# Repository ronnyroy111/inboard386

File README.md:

# Intel Inboard 386/PC Clone
https://forum.theretroweb.com/t/intel-inboard-386-pc-accelerator-clone/44

This is a project to reverse engineer and reproduce the [Intel Inboard 386/PC Accelerator Card](https://theretroweb.com/expansioncards/s/intel-inboard-386-pc).  
It's based on a damaged card that i obtained a while ago and managed to fix but decided to sacrifice for a reproduction.  
The Inboard 386/PC is an upgrade card from Intel for the IBM PC/XT and clones that upgraded the 8088 CPU to a 16MHz 386DX and up to 5MB of system memory.  
The card only uses standard 74 series logic chips along with some PALs/PROMs that were luckily not secured and were successfully dumped.  
The PCB is a 6 layer design with 4 signal layers. To aid with reverse engineering it i ended up choosing the destructive route and sanded the entire PCB down to the inner layers.  
By now the PCB design has been completed while the schematic still needs cleanup and further reverse engineering of the programmable logic to completely understand.  

The first revision of the board has been tested and confirmed to be working.  
GAL replacements for the PAL chips and a PROM replacement board have been tested as well.  
  
A memory expansion board is currently in work.

This current board design is a 1:1 copy of the original PCB, excluding some small details.  
A future plan is to do a redesign to condense parts of the logic into one or more CPLDs and integrate the optional external memory expansion boards into the design

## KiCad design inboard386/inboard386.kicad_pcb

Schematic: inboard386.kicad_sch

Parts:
C1, C2, C3, C4, C5, C6, C7, C8, C9, C10, C11, C12, C13, C14, C15, C16, C17, C18, C19, C20, C21, C22, C23, C24, C25, C26, C27, C28, C29, C30, C31, C32, C33, C34, C35, C36, C37, C38, C39, C40, C41, C42, C43, C44, C45, C46, C47, C48, C49, C50, C51, C53, C54, C55, C56, C57, C58, C59, C62, C63, C64, C66, C67, C68, C69, C70, C71, C72, C73: 100nF; C_Axial_L3.8mm_D2.6mm_P7.62mm_Horizontal_layer
C52: 22pF; C_Axial_L3.8mm_D2.6mm_P7.62mm_Horizontal_layer
C60, C61: 180pF; C_Axial_L3.8mm_D2.6mm_P7.62mm_Horizontal_layer
C65: 560µF; CP_Axial_L21.0mm_D8.0mm_P28.00mm_Horizontal_layer
CR1: 390 mV; D_DO-35_SOD27_P10.16mm_Horizontal_layer
H1, H2: MountingHole_Pad; MountingHole_3.2mm_M3_DIN965_Pad
J1, J2: Conn_02x20_Odd_Even; PinHeader_2x20_P2.54mm_inboard_mem
J3: CPU_Cable; IDC-Header_2x20_P2.54mm_Vertical_layer
J4: Bus_ISA_8bit; BUS_PC
R1: 115; R_Axial_DIN0207_L6.3mm_D2.5mm_P10.16mm_Horizontal_layer
R2: 12; R_Axial_DIN0207_L6.3mm_D2.5mm_P10.16mm_Horizontal_layer
R3: 1k; R_Axial_DIN0207_L6.3mm_D2.5mm_P10.16mm_Horizontal_layer
RP1, RP2, RP9, RP10: 2.2k; R_Array_SIP10_layer
RP3, RP4, RP5, RP6, RP7, RP8: 22; R_Array_SIP8_layer
RP11: 100; R_Array_SIP10_layer
RP12: 10k; R_Array_SIP10_layer
RP13, RP14: 3.3k; R_Array_SIP10_layer
U1, U2, U3, U4, U5, U6, U7, U8, U9, U10, U11, U12, U13, U14, U15, U16, U17, U18, U19, U20, U21, U22, U23, U24, U25, U26, U27, U28, U29, U30, U31, U32, U33, U34, U35, U36: TMM41256AP; DIP-16_W7.62mm_layer
U37, U38, U40, U44: 74F280; DIP-14_W7.62mm_layer
U39, U41, U78: 74AS1004; DIP-14_W7.62mm_layer
U42, U43: 74AS1032; DIP-14_W7.62mm_layer
U45, U62, U63, U66, U67, U92, U93: 74F74; DIP-14_W7.62mm_layer
U46, U48, U50, U53, U90: 74ALS244; DIP-20_W7.62mm_layer
U47, U49, U51, U52, U96, U97: 74ALS373; DIP-20_W7.62mm_layer
U54: 74F244; DIP-20_W7.62mm_layer
U55, U56, U57, U72, U95: 74ALS245; DIP-20_W7.62mm_layer
U58: 74F32; DIP-14_W7.62mm_layer
U59: 74AS21; DIP-14_W7.62mm_layer
U60: 74F00; DIP-14_W7.62mm_layer
U61, U64, U81, U82: 74F258; DIP-16_W7.62mm_layer
U65: 74AS1000; DIP-14_W7.62mm_layer
U68: 74F153; DIP-16_W7.62mm_layer
U69: 74LS174; DIP-16_W7.62mm_layer
U70: PAL16R8; DIP-20_W7.62mm_layer
U71: PAL20L8; DIP-24_W7.62mm_layer
U73: 80386; PGA-132_14x14_37.0x37.0mm
U74: PAL16R4; DIP-20_W7.62mm_layer
U75, U76: PAL16R6; DIP-20_W7.62mm_layer
U77, U84, U87, U91, U100: PAL16L8; DIP-20_W7.62mm_layer
U79: 74LS30; DIP-14_W7.62mm_layer
U80: 74F161; DIP-16_W7.62mm_layer
U83: 32MHz; Oscillator_DIP-14_layer
U85: 80387; PGA-68_11x11_29.2x29.2mm
U86, U101: TIBPAL16R4; DIP-20_W7.62mm_layer
U88, U89: 74ALS374; DIP-20_W7.62mm_layer
U94: 74F08; DIP-14_W7.62mm_layer
U98: 63S281; DIP-20_W7.62mm_layer
U99: TIBPAL16L8; DIP-20_W7.62mm_layer
U102: TIBPAL16R6; DIP-20_W7.62mm_layer

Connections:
387_ERR: U63.8 (~Q), U94.4
8088D_Cp: U86.1 (CLK), U89.11 (Cp), U100.16 (I/~O_{5})
8088D_OE: U89.1 (OE), U100.15 (I/~O_{4})
8088_A8: J3.16 (A8), U96.2 (O0)
8088_A9: J3.14 (A9), U96.5 (O1)
8088_A10: J3.12 (A10), U96.6 (O2)
8088_A11: J3.10 (A11), U96.9 (O3)
8088_A12: J3.8 (A12), U96.12 (O4)
8088_A13: J3.6 (A13), U96.15 (O5)
8088_A14: J3.4 (A14), U96.16 (O6)
8088_A15: J3.3 (A15), U96.19 (O7)
8088_A16/S3: J3.5 (A16/S3), U97.2 (O0)
8088_A17/S4: J3.7 (A17/S4), U97.5 (O1)
8088_A18/S5: J3.9 (A18/S5), U97.6 (O2)
8088_A19/S6: J3.11 (A19/S6), U97.9 (O3)
8088_AD0: J3.32 (AD0), U88.3 (D0), U89.2 (O0), U90.3 (O3b)
8088_AD1: J3.30 (AD1), U89.5 (O1), U90.5 (O2b), U94.1
8088_AD2: J3.28 (AD2), U88.7 (D2), U89.6 (O2), U90.18 (O0a)
8088_AD3: J3.26 (AD3), U88.8 (D3), U89.9 (O3), U90.16 (O1a)
8088_AD4: J3.24 (AD4), U88.13 (D4), U89.12 (O4), U90.14 (O2a)
8088_AD5: J3.22 (AD5), U88.14 (D5), U89.15 (O5), U90.12 (O3a)
8088_AD6: J3.20 (AD6), U88.17 (D6), U89.16 (O6), U90.9 (O0b)
8088_AD7: J3.18 (AD7), U88.18 (D7), U89.19 (O7), U90.7 (O1b)
8088_ALE: U70.17 (~O_{6}), U96.11 (LE), U97.11 (LE), U100.5 (I_{4})
+5V: C1.1, C2.1, C3.1, C4.1, C5.1, C6.1, C7.1, C8.1, C9.1, C10.1, C11.1, C12.1, C13.1, C14.1, C15.1, C16.1, C17.1, C18.1, C19.1, C20.1, C21.1, C22.1, C23.1, C24.1, C25.1, C26.1, C27.1, C28.1, C29.1, C30.1, C31.1, C32.1, C33.1, C34.1, C35.1, C36.1, C37.1, C38.1, C39.1, C40.1, C41.1, C42.1, C43.1, C44.1, C45.1, C46.1, C47.1, C48.1, C49.1, C50.1, C51.1, C53.1, C54.1, C55.1, C56.1, C57.1, C58.1, C59.1, C62.1, C63.1, C64.1, C65.1, C66.1, C67.1, C68.1, C69.1, C70.1, C71.1, C72.1, C73.1, CR1.1 (K), J1.5, J1.17, J1.29, J1.39, J2.9, J2.13, J2.17, J2.21, J2.29, J3.1 (VCC), J4.3 (VCC), J4.29 (VCC), R1.1, RP1.1 (common), RP2.1 (common), RP9.1 (common), RP10.1 (common), RP12.1 (common), RP13.1 (common), RP14.1 (common), U1.8 (V_{CC}), U2.8 (V_{CC}), U3.8 (V_{CC}), U4.8 (V_{CC}), U5.8 (V_{CC}), U6.8 (V_{CC}), U7.8 (V_{CC}), U8.8 (V_{CC}), U9.8 (V_{CC}), U10.8 (V_{CC}), U11.8 (V_{CC}), U12.8 (V_{CC}), U13.8 (V_{CC}), U14.8 (V_{CC}), U15.8 (V_{CC}), U16.8 (V_{CC}), U17.8 (V_{CC}), U18.8 (V_{CC}), U19.8 (V_{CC}), U20.8 (V_{CC}), U21.8 (V_{CC}), U22.8 (V_{CC}), U23.8 (V_{CC}), U24.8 (V_{CC}), U25.8 (V_{CC}), U26.8 (V_{CC}), U27.8 (V_{CC}), U28.8 (V_{CC}), U29.8 (V_{CC}), U30.8 (V_{CC}), U31.8 (V_{CC}), U32.8 (V_{CC}), U33.8 (V_{CC}), U34.8 (V_{CC}), U35.8 (V_{CC}), U36.8 (V_{CC}), U37.14 (VCC), U38.14 (VCC), U39.14 (VCC), U40.14 (VCC), U41.14 (VCC), U42.14 (VCC), U43.14 (VCC), U44.14 (VCC), U45.14 (VCC), U46.20 (VCC), U47.20 (VCC), U48.20 (VCC), U49.20 (VCC), U50.20 (VCC), U51.20 (VCC), U52.20 (VCC), U53.20 (VCC), U54.4 (I1a), U54.20 (VCC), U55.20 (VCC), U56.20 (VCC), U57.20 (VCC), U58.14 (VCC), U59.14 (VCC), U60.14 (VCC), U61.16 (VCC), U62.4 (~S), U62.13 (~R), U62.14 (VCC), U63.1 (~R), U63.13 (~R), U63.14 (VCC), U64.16 (VCC), U65.14 (VCC), U66.1 (~R), U66.4 (~S), U66.13 (~R), U66.14 (VCC), U67.10 (~S), U67.13 (~R), U67.14 (VCC), U68.16 (VCC), U69.14 (D5), U69.16 (VCC), U70.20 (V_{CC}), U71.24 (V_{CC}), U72.20 (VCC), U73.A1 (VCC), U73.A5 (VCC), U73.A7 (VCC), U73.A10 (VCC), U73.A14 (VCC), U73.C5 (VCC), U73.C12 (VCC), U73.D12 (VCC), U73.G2 (VCC), U73.G3 (VCC), U73.G12 (VCC), U73.G14 (VCC), U73.L12 (VCC), U73.M3 (VCC), U73.M7 (VCC), U73.M13 (VCC), U73.N4 (VCC), U73.N7 (VCC), U73.P2 (VCC), U73.P8 (VCC), U74.20 (V_{CC}), U75.20 (V_{CC}), U76.20 (V_{CC}), U77.20 (V_{CC}), U78.14 (VCC), U79.14 (VCC), U80.10 (CET), U80.16 (VCC), U81.16 (VCC), U82.16 (VCC), U83.14 (Vcc), U84.20 (V_{CC}), U85.A6 (VCC), U85.A9 (VCC), U85.B4 (VCC), U85.E1 (VCC), U85.F1 (VCC), U85.F10 (VCC), U85.J2 (VCC), U85.J11 (CKM), U85.K3 (TIE_HIGH), U85.K5 (VCC), U85.L4 (STEN), U85.L7 (VCC), U85.L9 (TIE_HIGH), U86.20 (V_{CC}), U87.20 (V_{CC}), U88.20 (VCC), U89.20 (VCC), U90.20 (VCC), U91.20 (V_{CC}), U92.4 (~S), U92.10 (~S), U92.13 (~R), U92.14 (VCC), U93.1 (~R), U93.10 (~S), U93.13 (~R), U93.14 (VCC), U94.14 (VCC), U95.20 (VCC), U96.20 (VCC), U97.20 (VCC), U98.20 (VCC), U99.20 (V_{CC}), U100.20 (V_{CC})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
A0: U70.15 (~O_{4}), U77.6 (I_{5}), U86.7 (I_{6}), U90.17 (I3b), U98.1 (A0), U99.2 (I_{1}), U100.7 (I_{6})
A1: U70.16 (~O_{5}), U77.5 (I_{4}), U86.6 (I_{5}), U90.15 (I2b), U98.2 (A1), U99.1 (I_{0}), U100.6 (I_{5})
A2: U64.13 (I1c), U73.C4 (A2), U74.5 (I_{4}), U85.L8 (CMD0#), U90.2 (I0a), U98.3 (A2), U100.8 (I_{7})
A3: U64.10 (I1d), U73.A3, U90.4 (I1a), U98.4 (A3)
A4: U64.6 (I1b), U73.B3 (A4), U90.6 (I2a), U98.5 (A4)
A5: U64.3 (I1a), U73.B2 (A5), U84.11 (I_{9}), U86.3 (I_{2}), U90.8 (I3a), U98.17 (A5)
A6: U61.13 (I1c), U73.C3 (A6), U84.9 (I_{8}), U90.11 (I0b), U98.18 (A6), U100.9 (I_{8}), U101.2 (I_{1})
A7: U61.10 (I1d), U73.C2 (A7), U84.8 (I_{7}), U90.13 (I1b), U98.19 (A7)
A8: U61.6 (I1b), U73.C1 (A8), U84.7 (I_{6}), U96.3 (D0)
A9: U64.14 (I0c), U73.D3 (A9), U84.6 (I_{5}), U96.4 (D1), U101.3 (I_{2})
A10: U64.11 (I0d), U73.D2 (A10), U84.5 (I_{4}), U96.7 (D2)
A11: U64.5 (I0b), U73.D1 (A11), U96.8 (D3)
A12: U64.2 (I0a), U73.E3 (A12), U96.13 (D4)
A13: U61.14 (I0c), U73.E2 (A13), U96.14 (D5)
A14: U61.11 (I0d), U73.E1 (A14), U96.17 (D6)
A15: U68.13 (I3b), U73.F1 (A15), U96.18 (D7)
A16: U68.3 (I3a), U71.7 (I_{6}), U73.G1 (A16), U97.3 (D0)
A17: U68.12 (I2b), U71.6 (I_{5}), U73.H1 (A17), U97.4 (D1)
A18: U71.5 (I_{4}), U73.H2 (A18), U97.7 (D2)
A19: U71.4 (I_{3}), U73.H3 (A19), U97.8 (D3)
A20: U61.2 (I0a), U71.3 (I_{2}), U73.J1 (A20)
A21: U61.3 (I1a), U71.2 (I_{1}), U73.K1 (A21)
A22: U71.1 (I_{0}), U73.K2 (A22)
A23: U71.8 (I_{7}), U73.L1 (A23)
A30: U73.P1 (A30), U97.17 (D6)
A30L: U58.5, U78.11, U97.16 (O6)
A31: U73.N2 (A31), U84.4 (I_{3}), U85.K6 (NPS2)
A->AD: U90.1 (OEa), U90.19 (OEb), U100.12 (~O_{1})
AEN: J4.42 (AEN), U58.1, U62.2 (D), U87.9 (I_{8}), U102.2 (I_{1})
AEN_BUF: U62.5 (Q), U75.5 (I_{4})
BA00: J4.62 (BA00), U91.8 (I_{7}), U99.4 (I_{3})
BA01: J4.61 (BA01), U91.9 (I_{8}), U99.3 (I_{2})
BA02: J4.60 (BA02), U82.13 (I1c)
BA03: J4.59 (BA03), U82.10 (I1d)
BA04: J4.58 (BA04), U82.6 (I1b)
BA05: J4.57 (BA05), U82.3 (I1a)
BA06: J4.56 (BA06), U81.13 (I1c)
BA07: J4.55 (BA07), U81.10 (I1d)
BA08: J4.54 (BA08), U81.6 (I1b)
BA09: J4.53 (BA09), U82.14 (I0c)
BA10: J4.52 (BA10), U82.11 (I0d)
BA11: J4.51 (BA11), U82.5 (I0b)
BA12: J4.50 (BA12), U82.2 (I0a)
BA13: J4.49 (BA13), U81.14 (I0c)
BA14: J4.48 (BA14), U81.11 (I0d)
BA15: J4.47 (BA15), U91.13 (I/~O_{2})
BA16: J4.46 (BA16), U91.18 (I/~O_{7})
BA17: J4.45 (BA17), U68.10 (I0b), U87.3 (I_{2})
BA18: J4.44 (BA18), U87.2 (I_{1})
BA19: J4.43 (BA19), U81.5 (I0b), U87.1 (I_{0})
BUSDIR: U55.1 (A->B), U56.1 (A->B), U57.1 (A->B), U72.1 (A->B), U95.1 (A->B), U99.15 (I/~O_{4})
CLK: U45.3 (C), U62.3 (C), U62.11 (C), U63.3 (C), U66.11 (C), U67.5 (Q), U74.6 (I_{5}), U75.9 (I_{8}), U76.9 (I_{8}), U80.2 (CP)
CLK2: R2.2, U66.3 (C), U67.3 (C), U67.11 (C), U73.F12 (CLK2), U74.1 (CLK), U75.1 (CLK), U76.1 (CLK), U85.K10 (CPUCLK2)
CLK88: C52.1, CR1.2 (A), J3.38 (CLK), R3.1, U78.1
CLK88_BUF: U78.4, U92.3 (C), U93.3 (C), U93.11 (C)
D0: U52.2 (O0), U53.17 (I3b), U69.3 (D0), U73.H12 (D0), U85.H2 (D0)
D1: U52.5 (O1), U53.15 (I2b), U69.4 (D1), U73.H13 (D1), U85.H1 (D1)
D2: U52.6 (O2), U53.13 (I1b), U69.6 (D2), U73.H14 (D2), U85.G2 (D2)
D3: U52.9 (O3), U53.11 (I0b), U69.11 (D3), U73.J14 (D3), U85.G1 (D3)
D4: U52.12 (O4), U53.8 (I3a), U69.13 (D4), U73.K14 (D4), U85.D2 (D4)
D5: U52.15 (O5), U53.6 (I2a), U73.K13 (D5), U85.D1 (D5)
D6: U52.16 (O6), U53.4 (I1a), U73.L14 (D6), U85.C2 (D6)
D7: U52.19 (O7), U53.2 (I0a), U73.K12 (D7), U85.C1 (D7)
D8: U50.17 (I3b), U51.2 (O0), U73.L13 (D8), U85.B1 (D8)
D9: U50.15 (I2b), U51.5 (O1), U73.N14 (D9), U85.A2 (D9)
D10: U50.13 (I1b), U51.6 (O2), U73.M12 (D10), U85.B3 (D10)
D11: U50.11 (I0b), U51.9 (O3), U73.N13 (D11), U85.A3 (D11)
D12: U50.8 (I3a), U51.12 (O4), U73.N12 (D12), U85.A4 (D12)
D13: U50.6 (I2a), U51.15 (O5), U73.P13 (D13), U85.B5 (D13)
D14: U50.4 (I1a), U51.16 (O6), U73.P12 (D14), U85.A5 (D14)
D15: U50.2 (I0a), U51.19 (O7), U73.M11 (D15), U85.B6 (D15)
D16: U48.17 (I3b), U49.2 (O0), U73.N11 (D16), U85.A7 (D16)
D17: U48.15 (I2b), U49.5 (O1), U73.N10 (D17), U85.B8 (D17)
D18: U48.13 (I1b), U49.6 (O2), U73.P11 (D18), U85.A8 (D18)
D19: U48.11 (I0b), U49.9 (O3), U73.P10 (D19), U85.B9 (D19)
D20: U48.8 (I3a), U49.12 (O4), U73.M9 (D20), U85.B10 (D20)
D21: U48.6 (I2a), U49.15 (O5), U73.N9 (D21), U85.A10 (D21)
D22: U48.4 (I1a), U49.16 (O6), U73.P9 (D22), U85.B11 (D22)
D23: U48.2 (I0a), U49.19 (O7), U73.N8 (D23), U85.C10 (D23)
D24: U46.17 (I3b), U47.2 (O0), U73.P7 (D24), U85.D10 (D24)
D25: U46.15 (I2b), U47.5 (O1), U73.N6 (D25), U85.D11 (D25)
D26: U46.13 (I1b), U47.6 (O2), U73.P5 (D26), U85.E10 (D26)
D27: U46.11 (I0b), U47.9 (O3), U73.N5 (D27), U85.E11 (D27)
D28: U46.8 (I3a), U47.12 (O4), U73.M6 (D28), U85.G10 (D28)
D29: U46.6 (I2a), U47.15 (O5), U73.P4 (D29), U85.G11 (D29)
D30: U46.4 (I1a), U47.16 (O6), U73.P3 (D30), U85.H10 (D30)
D31: U46.2 (I0a), U47.19 (O7), U73.M5 (D31), U85.H11 (D31)
D->MD_OE: U46.1 (OEa), U46.19 (OEb), U48.1 (OEa), U48.19 (OEb), U50.1 (OEa), U50.19 (OEb), U53.1 (OEa), U53.19 (OEb), U60.8
DACK0: U71.11 (I_{10}), U74.18 (I/~O_{7}), U78.8, U87.11 (I_{9}), U91.6 (I_{5})
DB0: J4.40 (DB0), RP13.3 (R2), U95.18 (B0)
DB0B: RP14.9 (R8), U55.18 (B0), U56.18 (B0), U57.18 (B0), U72.18 (B0), U79.1, U88.2 (O0), U89.3 (D0), U95.2 (A0), U98.6 (O1)
DB1: J4.39 (DB1), RP13.4 (R3), U95.17 (B1)
DB1B: RP14.8 (R7), U55.17 (B1), U56.17 (B1), U57.17 (B1), U72.17 (B1), U88.5 (O1), U89.4 (D1), U95.3 (A1), U98.7 (O2), U102.8 (I_{7})
DB2: J4.38 (DB2), RP13.5 (R4), U95.16 (B2)
DB2B: RP14.7 (R6), U55.16 (B2), U56.16 (B2), U57.16 (B2), U72.16 (B2), U79.2, U86.2 (I_{1}), U88.6 (O2), U95.4 (A2), U98.8 (O3)
DB3: J4.37 (DB3), RP13.6 (R5), U95.15 (B3)
DB3B: RP14.6 (R5), U55.15 (B3), U56.15 (B3), U57.15 (B3), U72.15 (B3), U79.3, U86.19 (I/~O_{8}), U88.9 (O3), U89.8 (D3), U95.5 (A3), U98.9 (O4)
DB4: J4.36 (DB4), RP13.7 (R6), U95.14 (B4)
DB4B: RP14.5 (R4), U55.14 (B4), U56.14 (B4), U57.14 (B4), U72.14 (B4), U79.4, U88.12 (O4), U89.13 (D4), U95.6 (A4), U98.11 (O5)
DB5: J4.35 (DB5), RP13.8 (R7), U95.13 (B5)
DB5B: RP14.4 (R3), U55.13 (B5), U56.13 (B5), U57.13 (B5), U72.13 (B5), U88.15 (O5), U89.14 (D5), U95.7 (A5), U98.12 (O6), U102.7 (I_{6})
DB6: J4.34 (DB6), RP13.9 (R8), U95.12 (B6)
DB6B: RP14.3 (R2), U55.12 (B6), U56.12 (B6), U57.12 (B6), U72.12 (B6), U79.5, U88.16 (O6), U89.17 (D6), U95.8 (A6), U98.13 (O7)
DB7: J4.33 (DB7), RP13.10 (R9), U95.11 (B7)
DB7B: RP14.2 (R1), U55.11 (B7), U56.11 (B7), U57.11 (B7), U72.11 (B7), U79.6, U86.18 (I/~O_{7}), U88.19 (O7), U89.18 (D7), U95.9 (A7), U98.14 (O8)
DB_EN: U87.12 (~O_{1}), U95.19 (CE)
D/~C: U73.A11 (D/~C), U77.9 (I_{8}), U84.2 (I_{1})
ERROR387: U63.11 (C), U78.6
FPU_STAT_SET: U42.13, U63.10 (~S), U74.16 (~O_{5})
GND: C1.2, C2.2, C3.2, C4.2, C5.2, C6.2, C7.2, C8.2, C9.2, C10.2, C11.2, C12.2, C13.2, C14.2, C15.2, C16.2, C17.2, C18.2, C19.2, C20.2, C21.2, C22.2, C23.2, C24.2, C25.2, C26.2, C27.2, C28.2, C29.2, C30.2, C31.2, C32.2, C33.2, C34.2, C35.2, C36.2, C37.2, C38.2, C39.2, C40.2, C41.2, C42.2, C43.2, C44.2, C45.2, C46.2, C47.2, C48.2, C49.2, C50.2, C51.2, C53.2, C54.2, C55.2, C56.2, C57.2, C58.2, C59.2, C60.2, C61.2, C62.2, C63.2, C64.2, C65.2, C66.2, C67.2, C68.2, C69.2, C70.2, C71.2, C72.2, C73.2, H1.1 (1_1), H2.1 (1_1), J1.2, J1.12, J1.24, J1.36, J2.2, J2.12, J2.16, J2.20, J2.28, J2.40, J3.2 (GND), J3.40 (GND), J4.1 (GND), J4.10 (GND), J4.31 (GND), R3.2, RP6.5 (R3.1), RP11.1 (common), U1.16 (V_{SS}), U2.16 (V_{SS}), U3.16 (V_{SS}), U4.16 (V_{SS}), U5.16 (V_{SS}), U6.16 (V_{SS}), U7.16 (V_{SS}), U8.16 (V_{SS}), U9.16 (V_{SS}), U10.16 (V_{SS}), U11.16 (V_{SS}), U12.16 (V_{SS}), U13.16 (V_{SS}), U14.16 (V_{SS}), U15.16 (V_{SS}), U16.16 (V_{SS}), U17.16 (V_{SS}), U18.16 (V_{SS}), U19.16 (V_{SS}), U20.16 (V_{SS}), U21.16 (V_{SS}), U22.16 (V_{SS}), U23.16 (V_{SS}), U24.16 (V_{SS}), U25.16 (V_{SS}), U26.16 (V_{SS}), U27.16 (V_{SS}), U28.16 (V_{SS}), U29.16 (V_{SS}), U30.16 (V_{SS}), U31.16 (V_{SS}), U32.16 (V_{SS}), U33.16 (V_{SS}), U34.16 (V_{SS}), U35.16 (V_{SS}), U36.16 (V_{SS}), U37.7 (GND), U38.7 (GND), U39.7 (GND), U40.7 (GND), U41.7 (GND), U42.7 (GND), U43.7 (GND), U44.7 (GND), U45.7 (GND), U46.10 (GND), U47.10 (GND), U48.10 (GND), U49.10 (GND), U50.10 (GND), U51.10 (GND), U52.10 (GND), U53.10 (GND), U54.2 (I0a), U54.6 (I2a), U54.8 (I3a), U54.10 (GND), U54.11 (I0b), U54.13 (I1b), U54.15 (I2b), U54.17 (I3b), U55.10 (GND), U56.10 (GND), U57.10 (GND), U58.7 (GND), U59.7 (GND), U60.7 (GND), U61.8 (GND), U62.7 (GND), U63.7 (GND), U63.12 (D), U64.8 (GND), U65.7 (GND), U66.7 (GND), U67.7 (GND), U68.8 (GND), U69.8 (GND), U70.10 (GND), U71.12 (GND), U72.10 (GND), U73.A2 (VSS), U73.A6 (VSS), U73.A9 (VSS), U73.B1 (VSS), U73.B5 (VSS), U73.B11 (VSS), U73.B14 (VSS), U73.C11 (VSS), U73.F2 (VSS), U73.F3 (VSS), U73.F14 (VSS), U73.J2 (VSS), U73.J3 (VSS), U73.J12 (VSS), U73.J13 (VSS), U73.M4 (VSS), U73.M8 (VSS), U73.M10 (VSS), U73.N3 (VSS), U73.P6 (VSS), U73.P14 (VSS), U74.10 (GND), U75.10 (GND), U76.10 (GND), U77.10 (GND), U78.7 (GND), U79.7 (GND), U80.8 (GND), U81.2 (I0a), U81.3 (I1a), U81.8 (GND), U82.8 (GND), U83.7 (GND), U84.10 (GND), U85.B2 (VSS), U85.B7 (VSS), U85.C11 (VSS), U85.E2 (VSS), U85.F2 (VSS), U85.F11 (VSS), U85.J1 (VSS), U85.J10 (VSS), U85.K9 (NC), U85.K11 (NUMCLK2), U85.L5 (VSS), U86.10 (GND), U87.10 (GND), U88.10 (GND), U89.10 (GND), U90.10 (GND), U91.10 (GND), U92.7 (GND), U93.7 (GND), U94.7 (GND), U95.10 (GND), U96.10 (GND), U97.10 (GND), U98.10 (GND), U99.10 (GND), U100.10 (GND), U101.10 (GND), U102.10 (GND)
HOLD: RP11.4 (R3), U73.D14 (HOLD)
INTR: U73.B7 (INTR), U101.19 (I/~O_{8})
INTR88: C61.1, J3.36 (INTR), U101.9 (I_{8})
IO: J4.32 (IO), U87.16 (I/~O_{5})
MA0: RP4.4 (R2.2), U1.5 (A0), U2.5 (A0), U3.5 (A0), U4.5 (A0), U5.5 (A0), U6.5 (A0), U7.5 (A0), U8.5 (A0), U9.5 (A0), U10.5 (A0), U11.5 (A0), U12.5 (A0), U13.5 (A0), U14.5 (A0), U15.5 (A0), U16.5 (A0), U17.5 (A0), U18.5 (A0), U19.5 (A0), U20.5 (A0), U21.5 (A0), U22.5 (A0), U23.5 (A0), U24.5 (A0), U25.5 (A0), U26.5 (A0), U27.5 (A0), U28.5 (A0), U29.5 (A0), U30.5 (A0), U31.5 (A0), U32.5 (A0), U33.5 (A0), U34.5 (A0), U35.5 (A0), U36.5 (A0)
MA1: RP4.6 (R3.2), U1.7 (A1), U2.7 (A1), U3.7 (A1), U4.7 (A1), U5.7 (A1), U6.7 (A1), U7.7 (A1), U8.7 (A1), U9.7 (A1), U10.7 (A1), U11.7 (A1), U12.7 (A1), U13.7 (A1), U14.7 (A1), U15.7 (A1), U16.7 (A1), U17.7 (A1), U18.7 (A1), U19.7 (A1), U20.7 (A1), U21.7 (A1), U22.7 (A1), U23.7 (A1), U24.7 (A1), U25.7 (A1), U26.7 (A1), U27.7 (A1), U28.7 (A1), U29.7 (A1), U30.7 (A1), U31.7 (A1), U32.7 (A1), U33.7 (A1), U34.7 (A1), U35.7 (A1), U36.7 (A1)
MA2: RP4.8 (R4.2), U1.6 (A2), U2.6 (A2), U3.6 (A2), U4.6 (A2), U5.6 (A2), U6.6 (A2), U7.6 (A2), U8.6 (A2), U9.6 (A2), U10.6 (A2), U11.6 (A2), U12.6 (A2), U13.6 (A2), U14.6 (A2), U15.6 (A2), U16.6 (A2), U17.6 (A2), U18.6 (A2), U19.6 (A2), U20.6 (A2), U21.6 (A2), U22.6 (A2), U23.6 (A2), U24.6 (A2), U25.6 (A2), U26.6 (A2), U27.6 (A2), U28.6 (A2), U29.6 (A2), U30.6 (A2), U31.6 (A2), U32.6 (A2), U33.6 (A2), U34.6 (A2), U35.6 (A2), U36.6 (A2)
MA3: RP7.2 (R1.2), U1.12 (A3), U2.12 (A3), U3.12 (A3), U4.12 (A3), U5.12 (A3), U6.12 (A3), U7.12 (A3), U8.12 (A3), U9.12 (A3), U10.12 (A3), U11.12 (A3), U12.12 (A3), U13.12 (A3), U14.12 (A3), U15.12 (A3), U16.12 (A3), U17.12 (A3), U18.12 (A3), U19.12 (A3), U20.12 (A3), U21.12 (A3), U22.12 (A3), U23.12 (A3), U24.12 (A3), U25.12 (A3), U26.12 (A3), U27.12 (A3), U28.12 (A3), U29.12 (A3), U30.12 (A3), U31.12 (A3), U32.12 (A3), U33.12 (A3), U34.12 (A3), U35.12 (A3), U36.12 (A3)
MA4: RP7.4 (R2.2), U1.11 (A4), U2.11 (A4), U3.11 (A4), U4.11 (A4), U5.11 (A4), U6.11 (A4), U7.11 (A4), U8.11 (A4), U9.11 (A4), U10.11 (A4), U11.11 (A4), U12.11 (A4), U13.11 (A4), U14.11 (A4), U15.11 (A4), U16.11 (A4), U17.11 (A4), U18.11 (A4), U19.11 (A4), U20.11 (A4), U21.11 (A4), U22.11 (A4), U23.11 (A4), U24.11 (A4), U25.11 (A4), U26.11 (A4), U27.11 (A4), U28.11 (A4), U29.11 (A4), U30.11 (A4), U31.11 (A4), U32.11 (A4), U33.11 (A4), U34.11 (A4), U35.11 (A4), U36.11 (A4)
MA5: RP7.6 (R3.2), U1.10 (A5), U2.10 (A5), U3.10 (A5), U4.10 (A5), U5.10 (A5), U6.10 (A5), U7.10 (A5), U8.10 (A5), U9.10 (A5), U10.10 (A5), U11.10 (A5), U12.10 (A5), U13.10 (A5), U14.10 (A5), U15.10 (A5), U16.10 (A5), U17.10 (A5), U18.10 (A5), U19.10 (A5), U20.10 (A5), U21.10 (A5), U22.10 (A5), U23.10 (A5), U24.10 (A5), U25.10 (A5), U26.10 (A5), U27.10 (A5), U28.10 (A5), U29.10 (A5), U30.10 (A5), U31.10 (A5), U32.10 (A5), U33.10 (A5), U34.10 (A5), U35.10 (A5), U36.10 (A5)
MA6: RP7.8 (R4.2), U1.13 (A6), U2.13 (A6), U3.13 (A6), U4.13 (A6), U5.13 (A6), U6.13 (A6), U7.13 (A6), U8.13 (A6), U9.13 (A6), U10.13 (A6), U11.13 (A6), U12.13 (A6), U13.13 (A6), U14.13 (A6), U15.13 (A6), U16.13 (A6), U17.13 (A6), U18.13 (A6), U19.13 (A6), U20.13 (A6), U21.13 (A6), U22.13 (A6), U23.13 (A6), U24.13 (A6), U25.13 (A6), U26.13 (A6), U27.13 (A6), U28.13 (A6), U29.13 (A6), U30.13 (A6), U31.13 (A6), U32.13 (A6), U33.13 (A6), U34.13 (A6), U35.13 (A6), U36.13 (A6)
MA7: RP5.2 (R1.2), U1.9 (A7), U2.9 (A7), U3.9 (A7), U4.9 (A7), U5.9 (A7), U6.9 (A7), U7.9 (A7), U8.9 (A7), U9.9 (A7), U10.9 (A7), U11.9 (A7), U12.9 (A7), U13.9 (A7), U14.9 (A7), U15.9 (A7), U16.9 (A7), U17.9 (A7), U18.9 (A7), U19.9 (A7), U20.9 (A7), U21.9 (A7), U22.9 (A7), U23.9 (A7), U24.9 (A7), U25.9 (A7), U26.9 (A7), U27.9 (A7), U28.9 (A7), U29.9 (A7), U30.9 (A7), U31.9 (A7), U32.9 (A7), U33.9 (A7), U34.9 (A7), U35.9 (A7), U36.9 (A7)
MA8: RP5.4 (R2.2), U1.1 (A8), U2.1 (A8), U3.1 (A8), U4.1 (A8), U5.1 (A8), U6.1 (A8), U7.1 (A8), U8.1 (A8), U9.1 (A8), U10.1 (A8), U11.1 (A8), U12.1 (A8), U13.1 (A8), U14.1 (A8), U15.1 (A8), U16.1 (A8), U17.1 (A8), U18.1 (A8), U19.1 (A8), U20.1 (A8), U21.1 (A8), U22.1 (A8), U23.1 (A8), U24.1 (A8), U25.1 (A8), U26.1 (A8), U27.1 (A8), U28.1 (A8), U29.1 (A8), U30.1 (A8), U31.1 (A8), U32.1 (A8), U33.1 (A8), U34.1 (A8), U35.1 (A8), U36.1 (A8)
MAEN_A/~BA: U60.9, U60.13, U65.9, U65.12, U68.2 (S1), U71.16 (I/~O_{2}), U75.14 (~O_{3}), U81.15 (OE), U82.15 (OE), U91.7 (I_{6})
MAEN_~A/BA: U42.12, U60.5, U61.15 (OE), U64.15 (OE), U65.11
MA_S0: U61.1 (S), U64.1 (S), U68.14 (S0), U75.18 (~O_{7}), U81.1 (S), U82.1 (S)
MBE0: J2.27, U42.2, U91.14 (I/~O_{3})
MBE1: J2.26, U42.10, U91.15 (I/~O_{4})
MBE2: J2.25, U43.2, U91.16 (I/~O_{5})
MBE3: J2.24, U43.10, U91.17 (I/~O_{6})
MD0: J1.40, RP1.9 (R8), U36.2 (D_{IN}), U36.14 (D_{OUT}), U44.8 (A), U52.3 (D0), U53.3 (O3b), U54.18 (O0a), U72.2 (A0)
MD1: J1.37, RP1.8 (R7), U35.2 (D_{IN}), U35.14 (D_{OUT}), U44.9 (B), U52.4 (D1), U53.5 (O2b), U54.16 (O1a), U72.3 (A1)
MD2: J1.38, RP1.7 (R6), U34.2 (D_{IN}), U34.14 (D_{OUT}), U44.10 (C), U52.7 (D2), U53.7 (O1b), U54.14 (O2a), U72.4 (A2)
MD3: J1.35, RP1.6 (R5), U33.2 (D_{IN}), U33.14 (D_{OUT}), U44.11 (D), U52.8 (D3), U53.9 (O0b), U54.12 (O3a), U72.5 (A3)
MD4: J1.34, RP1.5 (R4), U32.2 (D_{IN}), U32.14 (D_{OUT}), U44.12 (E), U52.13 (D4), U53.12 (O3a), U54.9 (O0b), U72.6 (A4)
MD5: J1.33, RP1.4 (R3), U31.2 (D_{IN}), U31.14 (D_{OUT}), U44.13 (F), U52.14 (D5), U53.14 (O2a), U54.7 (O1b), U72.7 (A5)
MD6: J1.32, RP1.3 (R2), U30.2 (D_{IN}), U30.14 (D_{OUT}), U44.1 (G), U52.17 (D6), U53.16 (O1a), U54.5 (O2b), U72.8 (A6)
MD7: J1.31, RP1.2 (R1), U29.2 (D_{IN}), U29.14 (D_{OUT}), U44.2 (H), U52.18 (D7), U53.18 (O0a), U54.3 (O3b), U72.9 (A7)
MD8: J1.30, RP9.9 (R8), U27.2 (D_{IN}), U27.14 (D_{OUT}), U38.8 (A), U50.3 (O3b), U51.3 (D0), U55.2 (A0)
MD9: J1.27, RP9.8 (R7), U26.2 (D_{IN}), U26.14 (D_{OUT}), U38.9 (B), U50.5 (O2b), U51.4 (D1), U55.3 (A1)
MD10: J1.28, RP9.7 (R6), U25.2 (D_{IN}), U25.14 (D_{OUT}), U38.10 (C), U50.7 (O1b), U51.7 (D2), U55.4 (A2)
MD11: J1.25, RP9.6 (R5), U24.2 (D_{IN}), U24.14 (D_{OUT}), U38.11 (D), U50.9 (O0b), U51.8 (D3), U55.5 (A3)
MD12: J1.26, RP9.5 (R4), U23.2 (D_{IN}), U23.14 (D_{OUT}), U38.12 (E), U50.12 (O3a), U51.13 (D4), U55.6 (A4)
MD13: J1.23, RP9.4 (R3), U22.2 (D_{IN}), U22.14 (D_{OUT}), U38.13 (F), U50.14 (O2a), U51.14 (D5), U55.7 (A5)
MD14: J1.22, RP9.3 (R2), U21.2 (D_{IN}), U21.14 (D_{OUT}), U38.1 (G), U50.16 (O1a), U51.17 (D6), U55.8 (A6)
MD15: J1.21, RP9.2 (R1), U20.2 (D_{IN}), U20.14 (D_{OUT}), U38.2 (H), U50.18 (O0a), U51.18 (D7), U55.9 (A7)
MD16: J1.20, RP10.9 (R8), U18.2 (D_{IN}), U18.14 (D_{OUT}), U40.8 (A), U48.3 (O3b), U49.3 (D0), U57.2 (A0)
MD17: J1.19, RP10.8 (R7), U17.2 (D_{IN}), U17.14 (D_{OUT}), U40.9 (B), U48.5 (O2b), U49.4 (D1), U57.3 (A1)
MD18: J1.18, RP10.7 (R6), U16.2 (D_{IN}), U16.14 (D_{OUT}), U40.10 (C), U48.7 (O1b), U49.7 (D2), U57.4 (A2)
MD19: J1.15, RP10.6 (R5), U15.2 (D_{IN}), U15.14 (D_{OUT}), U40.11 (D), U48.9 (O0b), U49.8 (D3), U57.5 (A3)
MD20: J1.16, RP10.5 (R4), U14.2 (D_{IN}), U14.14 (D_{OUT}), U40.12 (E), U48.12 (O3a), U49.13 (D4), U57.6 (A4)
MD21: J1.13, RP10.4 (R3), U13.2 (D_{IN}), U13.14 (D_{OUT}), U40.13 (F), U48.14 (O2a), U49.14 (D5), U57.7 (A5)
MD22: J1.14, RP10.3 (R2), U12.2 (D_{IN}), U12.14 (D_{OUT}), U40.1 (G), U48.16 (O1a), U49.17 (D6), U57.8 (A6)
MD23: J1.11, RP10.2 (R1), U11.2 (D_{IN}), U11.14 (D_{OUT}), U40.2 (H), U48.18 (O0a), U49.18 (D7), U57.9 (A7)
MD24: J1.10, RP2.9 (R8), U9.2 (D_{IN}), U9.14 (D_{OUT}), U37.8 (A), U46.3 (O3b), U47.3 (D0), U56.2 (A0)
MD25: J1.9, RP2.8 (R7), U8.2 (D_{IN}), U8.14 (D_{OUT}), U37.9 (B), U46.5 (O2b), U47.4 (D1), U56.3 (A1)
MD26: J1.8, RP2.7 (R6), U7.2 (D_{IN}), U7.14 (D_{OUT}), U37.10 (C), U46.7 (O1b), U47.7 (D2), U56.4 (A2)
MD27: J1.7, RP2.6 (R5), U6.2 (D_{IN}), U6.14 (D_{OUT}), U37.11 (D), U46.9 (O0b), U47.8 (D3), U56.5 (A3)
MD28: J1.6, RP2.5 (R4), U5.2 (D_{IN}), U5.14 (D_{OUT}), U37.12 (E), U46.12 (O3a), U47.13 (D4), U56.6 (A4)
MD29: J1.3, RP2.4 (R3), U4.2 (D_{IN}), U4.14 (D_{OUT}), U37.13 (F), U46.14 (O2a), U47.14 (D5), U56.7 (A5)
MD30: J1.4, RP2.3 (R2), U3.2 (D_{IN}), U3.14 (D_{OUT}), U37.1 (G), U46.16 (O1a), U47.17 (D6), U56.8 (A6)
MD31: J1.1, RP2.2 (R1), U2.2 (D_{IN}), U2.14 (D_{OUT}), U37.2 (H), U46.18 (O0a), U47.18 (D7), U56.9 (A7)
MEMLE: U58.13, U76.14 (~O_{3}), U78.13
MEMLE0: U52.11 (LE), U77.13 (I/~O_{2})
MEMLE1: U51.11 (LE), U77.14 (I/~O_{3})
MEMLE2: U49.11 (LE), U77.15 (I/~O_{4})
MEMW: U39.11, U39.13, U41.13, U99.16 (I/~O_{5})
MP0: J2.10, RP1.10 (R9), U28.14 (D_{OUT}), U44.4 (I)
MP0-3_H: U43.13, U59.6
MP0IN: J2.7, RP3.2 (R1.2), U28.2 (D_{IN})
MP1: J2.8, RP9.10 (R9), U19.14 (D_{OUT}), U38.4 (I)
MP1IN: J2.5, RP3.4 (R2.2), U19.2 (D_{IN})
MP2: J2.6, RP10.10 (R9), U10.14 (D_{OUT}), U40.4 (I)
MP2IN: J2.3, RP3.6 (R3.2), U10.2 (D_{IN})
MP3: J2.4, RP2.10 (R9), U1.14 (D_{OUT}), U37.4 (I)
MP3IN: J2.1, RP3.8 (R4.2), U1.2 (D_{IN})
M/~IO: U73.A12 (M/~IO), U77.8 (I_{7}), U84.1 (I_{0}), U85.L6 (NPS1#), U97.14 (D5), U102.3 (I_{2})
M/~IO_L: U97.15 (O5), U102.12 (I/~O_{1})
NMI: U73.B8 (NMI), U87.19 (~O_{8})
unnamed: J2.15, U71.15 (~O_{1})
unnamed: J2.18, U71.22 (~O_{8})
unnamed: J2.19, U71.21 (I/~O_{7})
unnamed: R1.2, R2.1, U65.6
unnamed: RP3.1 (R1.1), U44.6 (Odd), U59.1
unnamed: RP3.3 (R2.1), U38.6 (Odd), U59.2
unnamed: RP3.5 (R3.1), U40.6 (Odd), U59.4
unnamed: RP3.7 (R4.1), U37.6 (Odd), U59.5
unnamed: RP4.1 (R1.1), U42.6
unnamed: RP4.3 (R2.1), U41.2
unnamed: RP4.5 (R3.1), U41.4
unnamed: RP4.7 (R4.1), U41.6
unnamed: RP5.1 (R1.1), U39.6
unnamed: RP5.3 (R2.1), U39.8
unnamed: RP5.5 (R3.1), U41.12
unnamed: RP5.7 (R4.1), U43.6
unnamed: RP6.1 (R1.1), U39.12
unnamed: RP6.3 (R2.1), U39.10
unnamed: RP6.6 (R3.2), RP6.7 (R4.1)
unnamed: RP7.1 (R1.1), U41.8
unnamed: RP7.3 (R2.1), U41.10
unnamed: RP7.5 (R3.1), U39.2
unnamed: RP7.7 (R4.1), U39.4
unnamed: RP8.1 (R1.1), U42.3
unnamed: RP8.3 (R2.1), U42.8
unnamed: RP8.5 (R3.1), U43.3
unnamed: RP8.7 (R4.1), U43.8
unnamed: C52.2, RP11.2 (R1)
unnamed: U43.12, U65.8
unnamed: U45.5 (Q), U59.13
unnamed: U45.4 (~S), U60.1, U76.15 (~O_{4})
unnamed: U43.11, U45.12 (D)
unnamed: U45.8 (~Q), U87.6 (I_{5})
unnamed: U47.1 (OE), U49.1 (OE), U51.1 (OE), U52.1 (OE), U78.12
unnamed: U42.11, U54.1 (OEa), U54.19 (OEb)
unnamed: U55.19 (CE), U99.17 (I/~O_{6})
unnamed: U56.19 (CE), U99.19 (~O_{8})
unnamed: U57.19 (CE), U99.18 (I/~O_{7})
unnamed: U58.9, U94.6
unnamed: U59.12, U60.11
unnamed: U62.12 (D), U87.18 (I/~O_{7})
unnamed: U62.9 (Q), U75.4 (I_{3})
unnamed: U63.2 (D), U70.14 (~O_{3})
unnamed: U63.5 (Q), U76.6 (I_{5})
unnamed: U65.3, U65.4
unnamed: U66.5 (Q), U67.12 (D)
unnamed: U66.12 (D), U87.15 (I/~O_{4})
unnamed: U66.9 (Q), U80.7 (CEP), U87.14 (I/~O_{3})
unnamed: U67.2 (D), U67.6 (~Q)
unnamed: U69.5 (Q1), U80.3 (D0)
unnamed: U69.7 (Q2), U80.4 (D1)
unnamed: U69.10 (Q3), U80.5 (D2)
unnamed: U69.12 (Q4), U80.6 (D3)
unnamed: U60.2, U69.15 (Q5)
unnamed: U70.6 (I_{5}), U76.18 (~O_{7})
unnamed: U70.7 (I_{6}), U93.5 (Q)
unnamed: U58.3, U70.8 (I_{7})
unnamed: U70.9 (I_{8}), U77.4 (I_{3}), U92.5 (Q)
unnamed: U70.12 (~O_{1}), U77.2 (I_{1})
unnamed: U70.13 (~O_{2}), U77.1 (I_{0}), U92.1 (~R)
unnamed: U71.19 (I/~O_{5}), U75.12 (I/~O_{1}), U76.4 (I_{3})
unnamed: U42.5, U43.5, U71.20 (I/~O_{6})
unnamed: U72.19 (CE), U99.12 (~O_{1})
unnamed: U58.11, U74.3 (I_{2}), U75.7 (I_{6}), U99.11 (I_{9})
unnamed: U74.4 (I_{3}), U84.17 (I/~O_{6})
unnamed: U74.12 (I/~O_{1}), U94.10
unnamed: U74.13 (I/~O_{2}), U84.14 (I/~O_{3})
unnamed: U74.17 (~O_{6}), U84.13 (I/~O_{2})
unnamed: U75.6 (I_{5}), U76.17 (~O_{6})
unnamed: U75.8 (I_{7}), U80.15 (TC), U87.13 (I/~O_{2})
unnamed: U76.12 (I/~O_{1}), U84.18 (I/~O_{7})
unnamed: U60.12, U76.19 (I/~O_{8})
unnamed: U76.13 (~O_{2}), U77.7 (I_{6}), U93.2 (D), U99.5 (I_{4})
unnamed: U58.12, U60.10, U76.16 (~O_{5})
unnamed: U65.10, U77.11 (I_{9}), U97.13 (D4), U99.14 (I/~O_{3})
unnamed: U58.4, U77.12 (~O_{1}), U98.15 (~E1)
unnamed: U65.2, U83.8 (OUT)
unnamed: U84.19 (~O_{8}), U86.4 (I_{3})
unnamed: U86.12 (I/~O_{1}), U89.7 (D2)
unnamed: U86.14 (~O_{3}), U87.4 (I_{3})
unnamed: U88.4 (D1), U94.3
unnamed: U58.6, U88.1 (OE)
unnamed: U92.12 (D), U93.9 (Q)
unnamed: U94.8, U94.13
unnamed: U94.2, U97.19 (O7)
unnamed: U60.6, U99.6 (I_{5})
unnamed: U79.8, U100.1 (I_{0})
unnamed: U84.15 (I/~O_{4}), U100.2 (I_{1}), U101.4 (I_{3})
unnamed: U71.13 (I_{13}), U100.13 (I/~O_{2})
unnamed: U97.12 (O4), U100.14 (I/~O_{3})
unnamed: U97.18 (D7), U100.17 (I/~O_{6})
unnamed: U100.18 (I/~O_{7}), U102.6 (I_{5})
unnamed: U100.19 (~O_{8}), U102.5 (I_{4})
unnamed: U45.10 (~S), U75.13 (~O_{2}), U101.1 (CLK)
unnamed: U76.5 (I_{4}), U84.16 (I/~O_{5}), U101.6 (I_{5})
unnamed: U69.2 (Q0), U71.14 (I_{11}), U101.7 (I_{6})
unnamed: U59.9, U71.9 (I_{8}), U75.15 (~O_{4}), U101.12 (I/~O_{1})
unnamed: U80.9 (~PE), U101.13 (I/~O_{2})
unnamed: U69.9 (Cp), U101.14 (~O_{3})
unnamed: U45.2 (D), U70.19 (~O_{8}), U102.9 (I_{8})
unnamed: U58.2, U102.19 (I/~O_{8})
unnamed: U87.5 (I_{4}), U102.13 (~O_{2})
unnamed: U71.23 (I_{12}), U102.14 (~O_{3})
unnamed: U60.4, U77.3 (I_{2}), U102.15 (~O_{4})
PEREQ: U58.8, U73.C8 (PEREQ)
PEREQ387: U58.10, U85.K1 (PEREQ)
READY: J3.37 (READY), U92.2 (D)
RESET: U67.9 (Q), U73.C9 (RESET), U85.L10 (RESETIN)
RESET88: C60.1, J3.39 (RESET), RP12.10 (R9), U66.2 (D), U86.5 (I_{4}), U100.4 (I_{3}), U102.4 (I_{3})
RP6_8: RP6.8 (R4.2), U68.1 (Ea), U68.15 (Eb), U96.1 (OE), U97.1 (OE)
RP12_2: RP12.2 (R1), U65.13
RP12_6: RP12.6 (R5), U65.1
RP12_7: RP12.7 (R6), U65.5
RP12_8: RP12.8 (R7), U66.10 (~S), U80.1 (~MR)
RP12_9: RP12.9 (R8), U67.4 (~S), U93.4 (~S)
RP13_2: RP13.2 (R1), U45.1 (~R), U45.13 (~R)
U70_OE: RP11.3 (R2), U70.11 (~OE)
U74_OE: RP11.5 (R4), U74.11 (~OE)
U75_OE: RP11.9 (R8), U75.11 (~OE)
U76_OE: RP11.10 (R9), U76.11 (~OE)
U86_OE: RP11.8 (R7), U86.11 (~OE)
U101_OE: RP11.6 (R5), U101.11 (~OE)
U102_OE: RP11.7 (R6), U102.11 (~OE)
W/~R: U71.10 (I_{9}), U73.B10 (~W/R), U76.8 (I_{7}), U84.3 (I_{2}), U85.K4 (W/R#), U91.5 (I_{4}), U99.9 (I_{8}), U100.3 (I_{2})
~387_ERR: U63.9 (Q), U74.9 (I_{8}), U94.12, U101.8 (I_{7})
~A30L: U78.10, U98.16 (~E2)
~ADS: U73.E14 (~ADS), U74.7 (I_{6}), U75.3 (I_{2}), U76.2 (I_{1}), U85.K7 (ADS#)
~BE0: U70.5 (I_{4}), U73.E12 (~BE0), U91.4 (I_{3})
~BE1: U70.4 (I_{3}), U73.C13 (~BE1), U91.3 (I_{2}), U101.5 (I_{4})
~BE2: U70.3 (I_{2}), U73.B13 (~BE2), U91.2 (I_{1})
~BE3: U70.2 (I_{1}), U73.A13 (~BE3), U91.1 (I_{0})
~BS16: J3.13 (~SS0), J3.17 (~RD), J3.31 (QS0), J3.33 (QS1), RP14.10 (R9), U47.11 (LE), U73.C14 (~BS16), U79.11, U79.12
~BUSY387: RP12.3 (R2), U85.K2 (BUSY#), U94.5, U94.9
~BUSY: U73.B9 (~BUSY), U94.11
~CAS0: RP8.2 (R1.2), U28.15 (~CAS), U29.15 (~CAS), U30.15 (~CAS), U31.15 (~CAS), U32.15 (~CAS), U33.15 (~CAS), U34.15 (~CAS), U35.15 (~CAS), U36.15 (~CAS)
~CAS1: RP8.4 (R2.2), U19.15 (~CAS), U20.15 (~CAS), U21.15 (~CAS), U22.15 (~CAS), U23.15 (~CAS), U24.15 (~CAS), U25.15 (~CAS), U26.15 (~CAS), U27.15 (~CAS)
~CAS2: RP8.6 (R3.2), U10.15 (~CAS), U11.15 (~CAS), U12.15 (~CAS), U13.15 (~CAS), U14.15 (~CAS), U15.15 (~CAS), U16.15 (~CAS), U17.15 (~CAS), U18.15 (~CAS)
~CAS3: RP8.8 (R4.2), U1.15 (~CAS), U2.15 (~CAS), U3.15 (~CAS), U4.15 (~CAS), U5.15 (~CAS), U6.15 (~CAS), U7.15 (~CAS), U8.15 (~CAS), U9.15 (~CAS)
~CAS: J2.11, U42.1, U42.9, U43.1, U43.9, U45.11 (C), U75.16 (~O_{5}), U91.11 (I_{9}), U99.13 (I/~O_{2})
~CLK88: U70.1 (CLK), U77.16 (I/~O_{5}), U78.2, U78.3, U88.11 (Cp), U92.11 (C), U100.11 (I_{9}), U102.1 (CLK)
~CPU_MEMRW: U75.2 (I_{1}), U76.7 (I_{6}), U84.12 (~O_{1})
~DACK0: J4.19 (~DACK0), U78.9
~DACK2: J4.26 (~DACK2), U86.8 (I_{7})
~DACK3: J4.15 (~DACK3), U86.9 (I_{8})
~ERROR387: RP12.4 (R3), U74.19 (I/~O_{8}), U78.5, U85.L2 (ERROR#)
~ERROR: U73.A8 (~ERROR), U74.14 (~O_{3})
~LOCK88: J3.23 (~LOCK), U92.9 (Q)
~LOCK: U73.C10 (~LOCK), U93.12 (D)
~MA0: J2.39, U41.1, U64.12 (Zc), U82.12 (Zc)
~MA1: J2.38, U41.3, U64.9 (Zd), U82.9 (Zd)
~MA2: J2.37, U41.5, U64.7 (Zb), U82.7 (Zb)
~MA3: J2.36, U41.9, U64.4 (Za), U82.4 (Za)
~MA4: J2.35, U41.11, U61.12 (Zc), U81.12 (Zc)
~MA5: J2.34, U39.1, U61.9 (Zd), U81.9 (Zd)
~MA6b: U68.11 (I1b), U91.12 (~O_{1})
~MA6: J2.33, U39.3, U68.9 (Zb)
~MA7a: U68.6 (I0a), U86.13 (I/~O_{2})
~MA7b: U68.5 (I1a), U91.19 (~O_{8})
~MA7c: U68.4 (I2a), U71.17 (I/~O_{3})
~MA7: J2.32, U39.5, U68.7 (Za)
~MA8a: U61.5 (I0b), U71.18 (I/~O_{4})
~MA8: J2.31, U39.9, U61.7 (Zb), U81.7 (Zb)
~MA9?: J2.30, U61.4 (Za), U81.4 (Za)
~MEMW_E0: J2.23, RP6.2 (R1.2)
~MEMW_E1: J2.22, RP6.4 (R2.2)
~MEMW: RP5.6 (R3.2), U1.3 (~WRITE), U2.3 (~WRITE), U3.3 (~WRITE), U4.3 (~WRITE), U5.3 (~WRITE), U6.3 (~WRITE), U7.3 (~WRITE), U8.3 (~WRITE), U9.3 (~WRITE), U10.3 (~WRITE), U11.3 (~WRITE), U12.3 (~WRITE), U13.3 (~WRITE), U14.3 (~WRITE), U15.3 (~WRITE), U16.3 (~WRITE), U17.3 (~WRITE), U18.3 (~WRITE), U19.3 (~WRITE), U20.3 (~WRITE), U21.3 (~WRITE), U22.3 (~WRITE), U23.3 (~WRITE), U24.3 (~WRITE), U25.3 (~WRITE), U26.3 (~WRITE), U27.3 (~WRITE), U28.3 (~WRITE), U29.3 (~WRITE), U30.3 (~WRITE), U31.3 (~WRITE), U32.3 (~WRITE), U33.3 (~WRITE), U34.3 (~WRITE), U35.3 (~WRITE), U36.3 (~WRITE)
~NA: U60.3, U73.D13 (~NA)
~RAS?: J2.14, U42.4, U43.4, U75.17 (~O_{6})
~RASH: RP5.8 (R4.2), U1.4 (~RAS), U2.4 (~RAS), U3.4 (~RAS), U4.4 (~RAS), U5.4 (~RAS), U6.4 (~RAS), U7.4 (~RAS), U8.4 (~RAS), U9.4 (~RAS), U10.4 (~RAS), U11.4 (~RAS), U12.4 (~RAS), U13.4 (~RAS), U14.4 (~RAS), U15.4 (~RAS), U16.4 (~RAS), U17.4 (~RAS), U18.4 (~RAS)
~RASL: RP4.2 (R1.2), U19.4 (~RAS), U20.4 (~RAS), U21.4 (~RAS), U22.4 (~RAS), U23.4 (~RAS), U24.4 (~RAS), U25.4 (~RAS), U26.4 (~RAS), U27.4 (~RAS), U28.4 (~RAS), U29.4 (~RAS), U30.4 (~RAS), U31.4 (~RAS), U32.4 (~RAS), U33.4 (~RAS), U34.4 (~RAS), U35.4 (~RAS), U36.4 (~RAS)
~READYO: RP12.5 (R4), U59.10, U85.L3 (READYO#)
~READY: U59.8, U73.G13 (~READY), U74.8 (I_{7}), U76.3 (I_{2}), U85.K8 (READY#)
~RESET: U62.1 (~R), U62.10 (~S), U63.4 (~S), U67.1 (~R), U67.8 (~Q), U69.1 (~Mr), U74.2 (I_{1}), U75.19 (I/~O_{8})
~S0: J3.29 (~S0), U77.17 (I/~O_{6})
~S1: J3.27 (~S1), U77.19 (~O_{8})
~S2: J3.25 (~S2), U77.18 (I/~O_{7})
~SMEMR: J4.12 (~SMEMR), U87.8 (I_{7}), U99.8 (I_{7})
~SMEMW: J4.11 (~SMEMW), U87.7 (I_{6}), U99.7 (I_{6})

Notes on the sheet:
U75 Outputs: 13-18
!!! pinout of the diode is marked weird on the board
U76 Outputs: 13-19
U102 Outputs: 13-19
U99 Outputs: 12 14-19
!!!!!!
U91 Outputs: 12 14-17 19
U101 Outputs: 13-17 19
U70 Outputs: 12-19
U71 Outputs: 15 17-22
????
U100 Outputs: 12-13 15-19
U87 Outputs: 12 15-19 16 cond. OE
U74 Outputs: 12-17
U77 Outputs: 12-15 17-19
U86 Outputs: 12-17
U84 Outputs: 12 15-19

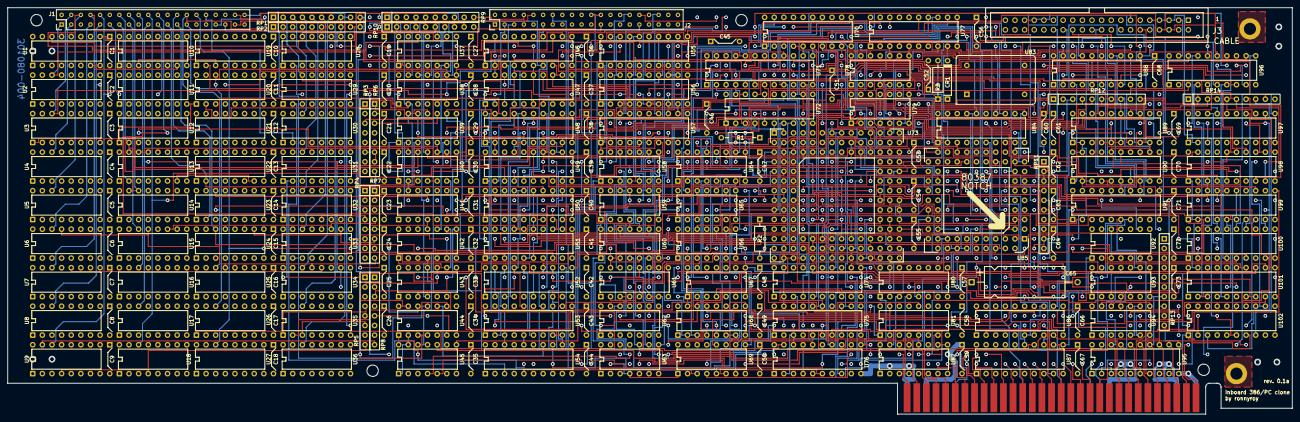
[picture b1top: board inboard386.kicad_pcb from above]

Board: 6 copper layers, 338.8 x 107.2 mm, 199 parts (0 on the bottom side), 382 nets.

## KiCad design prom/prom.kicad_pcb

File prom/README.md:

A small adapter PCB to replace the 63S281 PROM at U98 with a modern PLCC EEPROM.

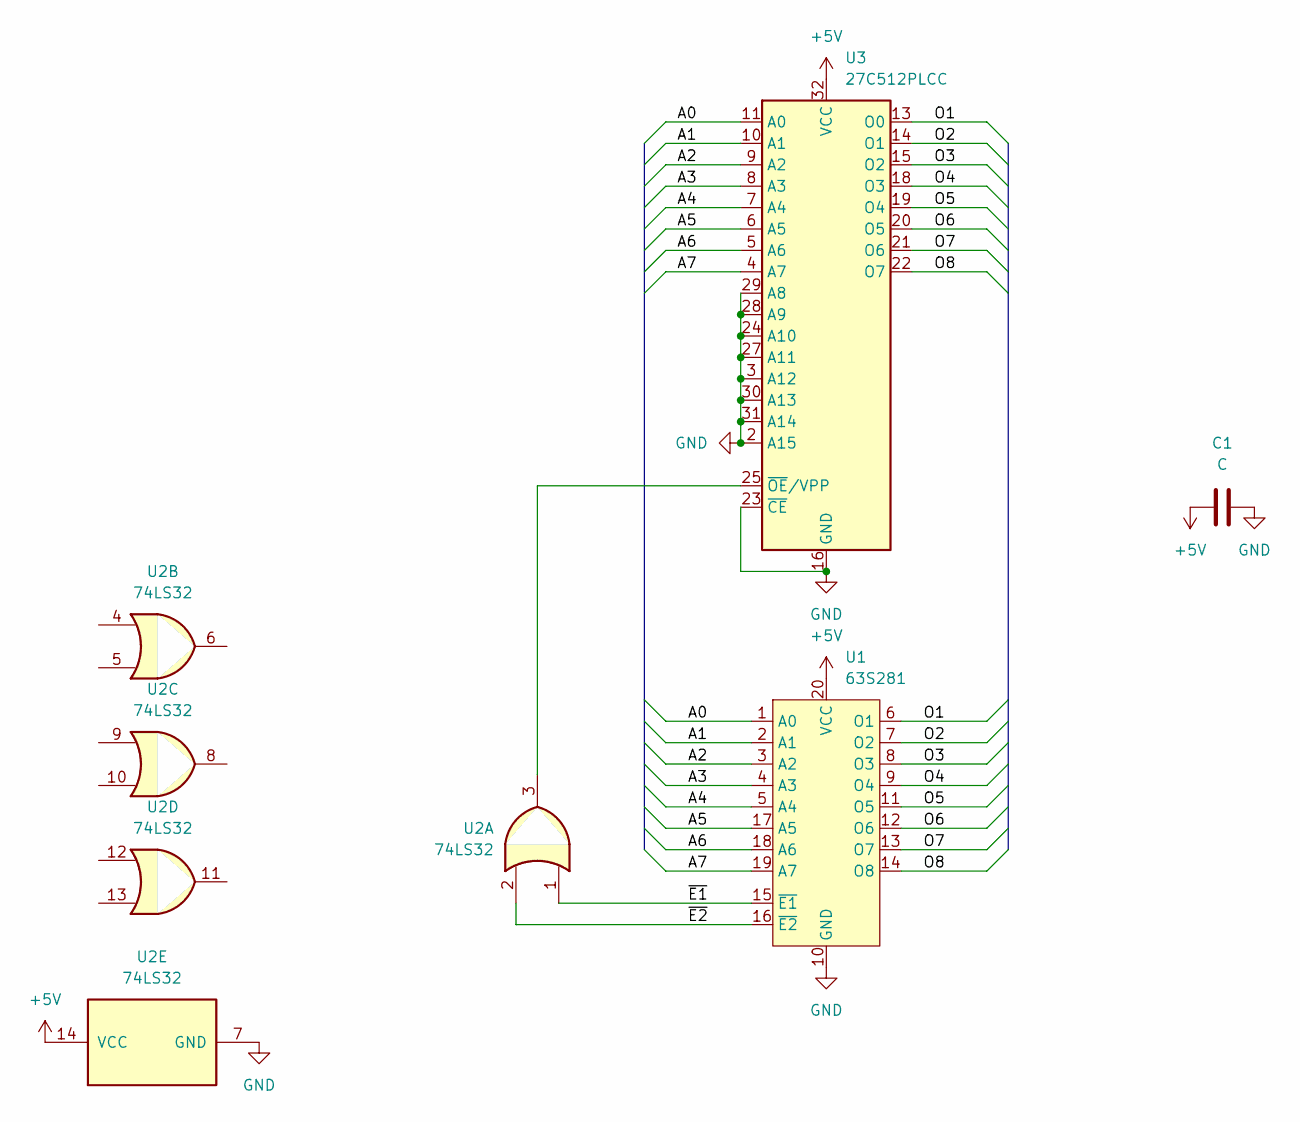
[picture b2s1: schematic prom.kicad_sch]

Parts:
C1: C; C_0805_2012Metric_Pad1.18x1.45mm_HandSolder
U1: 63S281; DIP-20_W7.62mm
U2: 74LS32; SOIC-14_3.9x8.7mm_P1.27mm
U3: 27C512PLCC; PLCC-32_11.4x14.0mm_P1.27mm

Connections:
+5V: C1.1, U1.20 (VCC), U2.14 (VCC), U3.32 (VCC)
/A0: U1.1 (A0), U3.11 (A0)
/A1: U1.2 (A1), U3.10 (A1)
/A2: U1.3 (A2), U3.9 (A2)
/A3: U1.4 (A3), U3.8 (A3)
/A4: U1.5 (A4), U3.7 (A4)
/A5: U1.17 (A5), U3.6 (A5)
/A6: U1.18 (A6), U3.5 (A6)
/A7: U1.19 (A7), U3.4 (A7)
/O1: U1.6 (O1), U3.13 (O0)
/O2: U1.7 (O2), U3.14 (O1)
/O3: U1.8 (O3), U3.15 (O2)
/O4: U1.9 (O4), U3.18 (O3)
/O5: U1.11 (O5), U3.19 (O4)
/O6: U1.12 (O6), U3.20 (O5)
/O7: U1.13 (O7), U3.21 (O6)
/O8: U1.14 (O8), U3.22 (O7)
/~E1: U1.15 (~E1), U2.1
/~E2: U1.16 (~E2), U2.2
GND: C1.2, U1.10 (GND), U2.7 (GND), U3.2 (A15), U3.3 (A12), U3.16 (GND), U3.23 (~CE), U3.24 (A10), U3.27 (A11), U3.28 (A9), U3.29 (A8), U3.30 (A13), U3.31 (A14)
unnamed: U2.3, U3.25 (~OE/VPP)

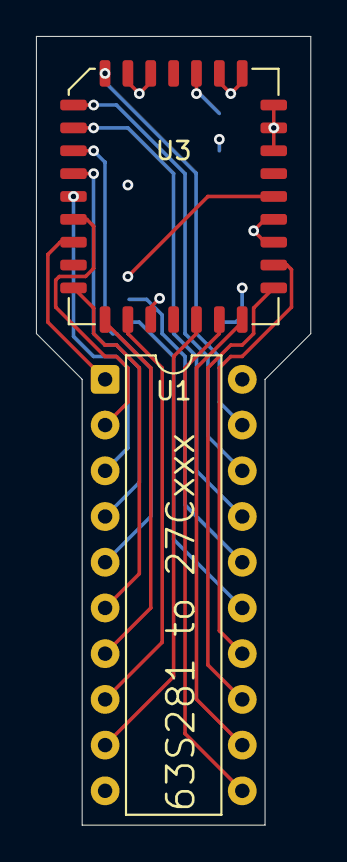
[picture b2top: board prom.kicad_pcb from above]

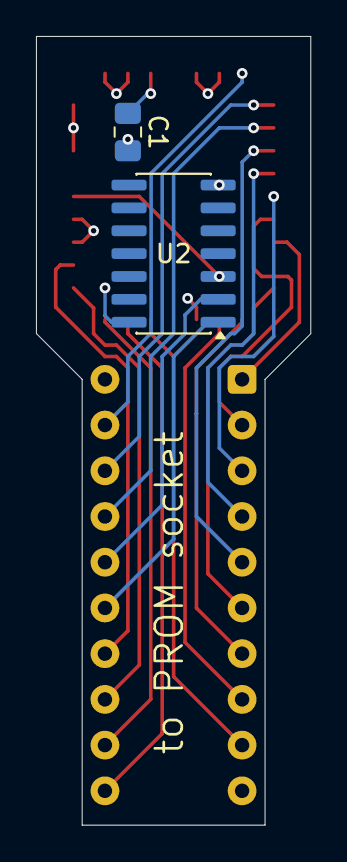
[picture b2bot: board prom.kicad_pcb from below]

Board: 4 copper layers, 15.2 x 43.8 mm, 4 parts (2 on the bottom side), 21 nets.

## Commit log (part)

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2026-05-24 Initial project commit. PCB design rev. 0.1
2026-05-24 Add README
    Added project details for Intel Inboard 386/PC Clone including reverse engineering efforts and future plans.
2026-05-24 Fix typo in README.md
2026-05-24 Add README for PROM adapter
2026-05-24 Add raw PAL dumps and extracted logic equations
2026-05-24 update README, add images
2026-05-24 update image
2026-06-13 minimal updates to schematic labelling
2026-06-13 Add CUPL code and compiled jed files.
2026-06-13 Add pictures of assmebled and running board
2026-06-13 fix image scaling
2026-06-13 Update README with board images and project status
2026-06-16 Add MIT License to the project
2026-06-16 Add parts list spreadsheet
2026-06-16 Add PROM adapter components to parts list
